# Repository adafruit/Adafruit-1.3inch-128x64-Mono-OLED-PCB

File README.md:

# PCB for the Adafruit 128x64 I2C/SPI 1.3" OLED breakout board

<a href="http://www.adafruit.com/products/938"><br/>
<a href="http://www.adafruit.com/products/938"><br/>
  Click here to purchase one from the Adafruit shop</a>

__Format is EagleCAD schematic and board layout__

These displays are small, only about 1.3" diagonal, but very readable due to the high contrast of an OLED display. This display is made of 128x64 individual white OLED pixels, each one is turned on or off by the controller chip. Because the display makes its own light, no backlight is required. This reduces the power required to run the OLED and is why the display has such high contrast; we really like this miniature display for its crispness!

The driver chip, SSD1306 can communicate in two ways: I2C or SPI. The OLED itself require a 3.3V power supply and 3.3V logic levels for communication, but we include a 3.3V regulator and all pins are fully level shifted so you can use with 5V devices!

We've updated the design to add auto-reset circuitry so that the reset pin is optional. The default interface is now I2C not SPI - since it speaks I2C you can easily connect it up with just two wires (plus power and ground!).  We've even included SparkFun qwiic compatible STEMMA QT connectors for the I2C bus so you don't even need to solder! 

The power requirements depend a little on how much of the display is lit but on average the display uses about 40mA from the 3.3V supply. Built into the OLED driver is a simple switch-cap charge pump that turns 3.3v-5v into a high voltage drive for the OLEDs.

[We have a detailed tutorial and example code in the form of an Arduino library](http://learn.adafruit.com/monochrome-oled-breakouts) for text and graphics. You'll need a microcontroller with more than 1K of RAM since the display must be buffered. The library can print text, bitmaps, pixels, rectangles, circles and lines. It uses 1K of RAM since it needs to buffer the entire display but its very fast! The code is simple to adapt to any other microcontroller.

## License
Adafruit invests time and resources providing this open source design,
please support Adafruit and open-source hardware by purchasing
products from Adafruit!

Designed by Adafruit Industries.
Creative Commons Attribution, Share-Alike license, check license.txt for more information
All text above must be included in any redistribution

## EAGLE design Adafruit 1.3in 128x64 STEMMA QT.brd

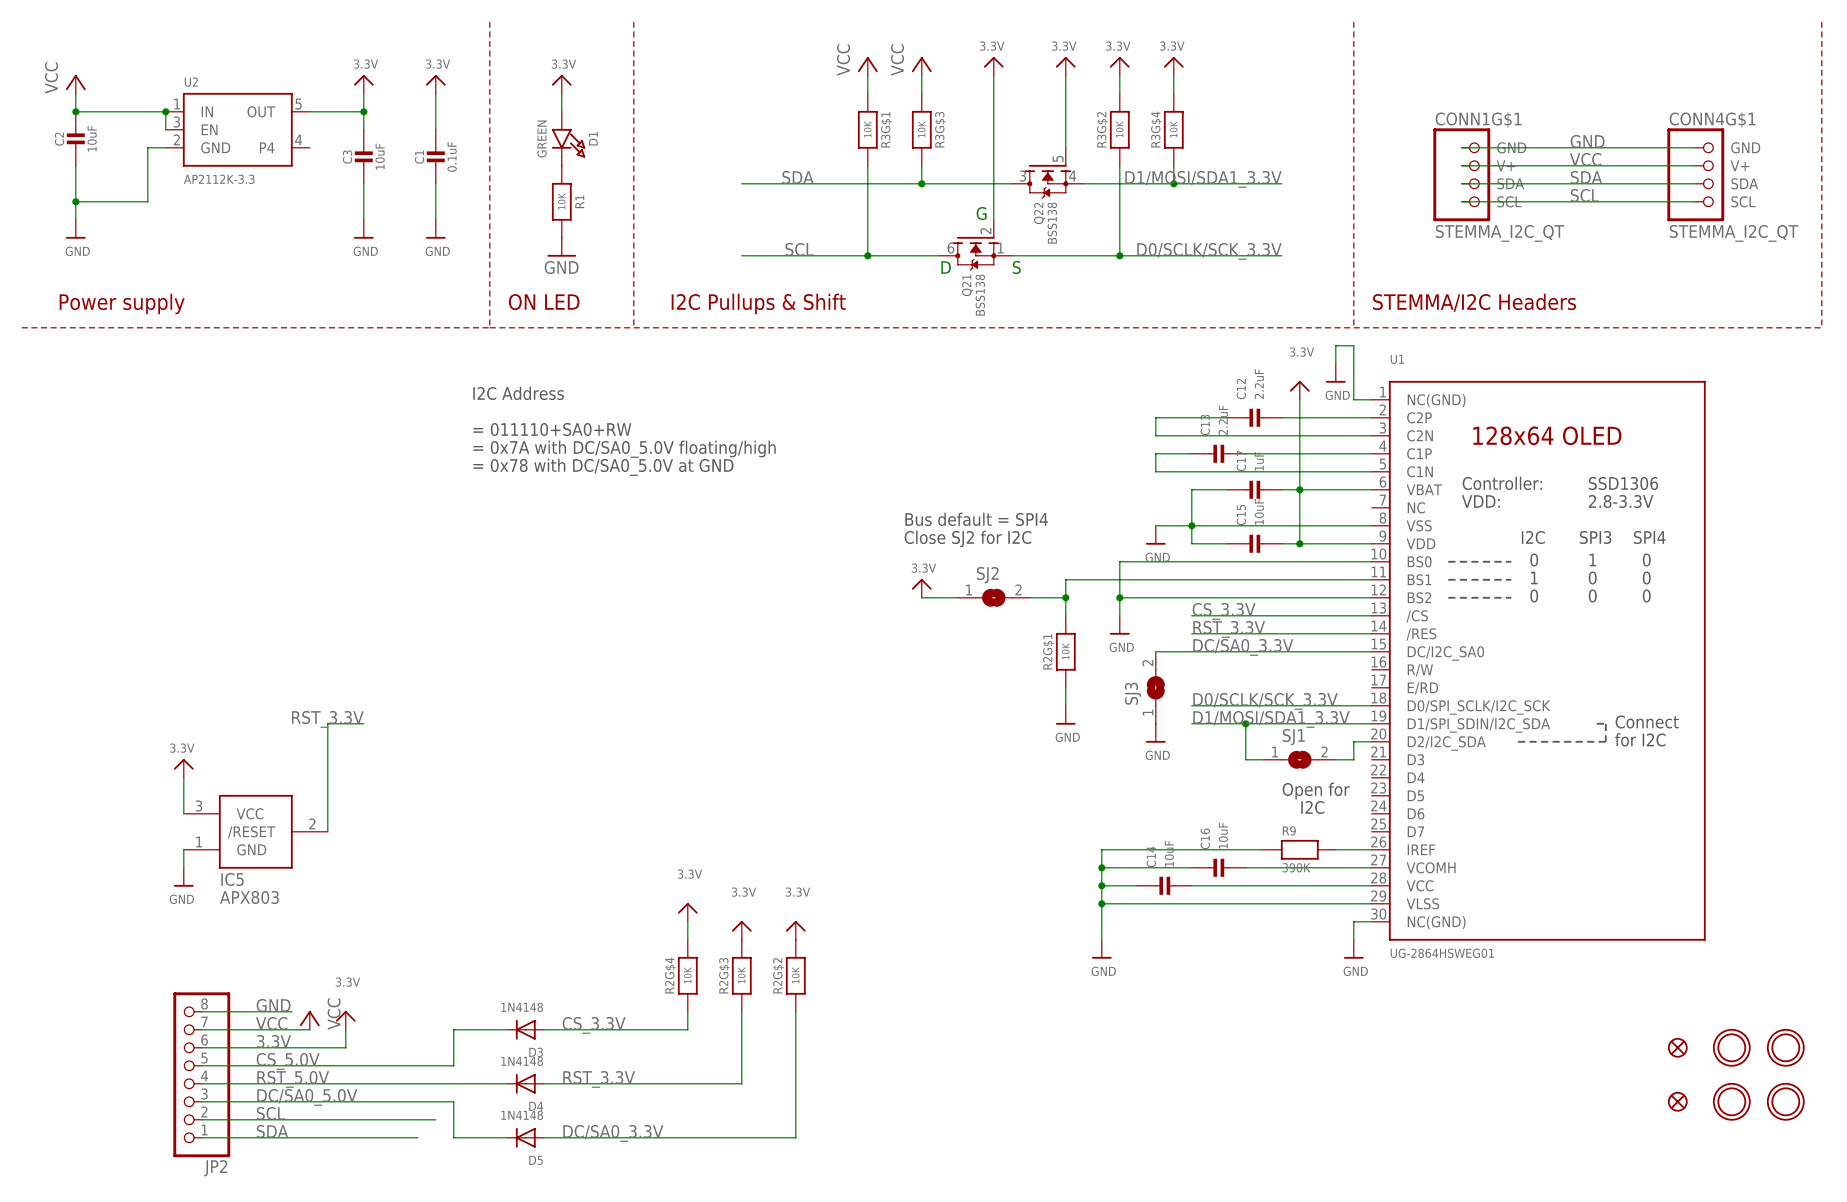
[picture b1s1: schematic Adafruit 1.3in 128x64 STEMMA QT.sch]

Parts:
C1: 0.1uF; 0603-NO
C2, C3, C14, C15, C16: 10uF; 0805-NO
C12, C13: 2.2uF; 0805-NO
C17: 1uF; 0603-NO
CONN1, CONN4: STEMMA_I2C_QT; JST_SH4
D1: GREEN; CHIPLED_0603_NOOUTLINE
D3, D4, D5: 1N4148; SOD-323
FID3, FID4: FIDUCIAL_1MM
IC5: APX803; SOT23
JP2: HEADER-1X870MIL; 1X08_ROUND_70
Q2: BSS138; SOT363
R1: 10K; 0603-NO
R2, R3: 10K; RESPACK_4X0603
R9: 390K; 0603-NO
SJ1, SJ2: SOLDERJUMPERCLOSED; SOLDERJUMPER_CLOSEDWIRE
SJ3: SOLDERJUMPER; SOLDERJUMPER_ARROW_NOPASTE
U1: UG-2864HSWEG01; UG-2864HSWEG01_1.3_WRAPAROUND
U2: AP2112K-3.3; SOT23-5
U$1, U$17, U$19, U$21: MOUNTINGHOLE2.5; MOUNTINGHOLE_2.5_PLATED

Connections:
3.3V: C1.1, C3.1, C15.2, C17.2, D1.A, IC5.3 (VCC), JP2.6, Q2.2 (G), Q2.5 (G), R2.5 (2), R2.6 (2), R2.7 (2), R3.2 (1), R3.4 (1), SJ2.1, U1.6 (VBAT), U1.9 (VDD), U2.5 (OUT)
CS_3.3V: D3.A, R2.4 (1), U1.13 (/CS)
CS_5.0V: D3.C, JP2.5
D0/SCLK/SCK_3.3V: Q2.1 (S), R3.7 (2), U1.18 (D0/SPI_SCLK/I2C_SCK)
D1/MOSI/SDA1_3.3V: Q2.4 (S), R3.5 (2), SJ1.1, U1.19 (D1/SPI_SDIN/I2C_SDA)
DC/SA0_3.3V: D5.A, R2.2 (1), SJ3.2, U1.15 (DC/I2C_SA0)
DC/SA0_5.0V: D5.C, JP2.3
GND: C1.2, C2.2, C3.2, C14.1, C15.1, C16.1, C17.1, CONN1.1 (GND), CONN4.1 (GND), IC5.1 (GND), JP2.8, R1.2, R2.1, R9.1, SJ3.1, U1.1 (NC(GND)), U1.8 (VSS), U1.10 (BS0), U1.12 (BS2), U1.29 (VLSS), U1.30 (NC(GND)), U2.2 (GND)
unnamed: D1.C, R1.1
unnamed: R2.8 (2), SJ2.2, U1.11 (BS1)
unnamed: R9.2, U1.26 (IREF)
unnamed: C12.2, U1.2 (C2P)
unnamed: C12.1, U1.3 (C2N)
unnamed: C13.2, U1.4 (C1P)
unnamed: C13.1, U1.5 (C1N)
unnamed: C14.2, U1.28 (VCC)
unnamed: C16.2, U1.27 (VCOMH)
unnamed: SJ1.2, U1.20 (D2/I2C_SDA)
RST_3.3V: D4.A, IC5.2 (/RESET), R2.3 (1), U1.14 (/RES)
RST_5.0V: D4.C, JP2.4
SCL: CONN1.4 (SCL), CONN4.4 (SCL), JP2.2, Q2.6 (D), R3.8 (2)
SDA: CONN1.3 (SDA), CONN4.3 (SDA), JP2.1, Q2.3 (D), R3.6 (2)
VCC: C2.1, CONN1.2 (V+), CONN4.2 (V+), JP2.7, R3.1, R3.3 (1), U2.1 (IN), U2.3 (EN)

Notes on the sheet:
I2C Pullups & Shift
STEMMA/I2C Headers
ON LED
Power supply
Bus default = SPI4
Close SJ2 for I2C
= 011110+SA0+RW
= 0x7A with DC/SA0_5.0V floating/high
= 0x78 with DC/SA0_5.0V at GND
I2C Address
Open for
I2C

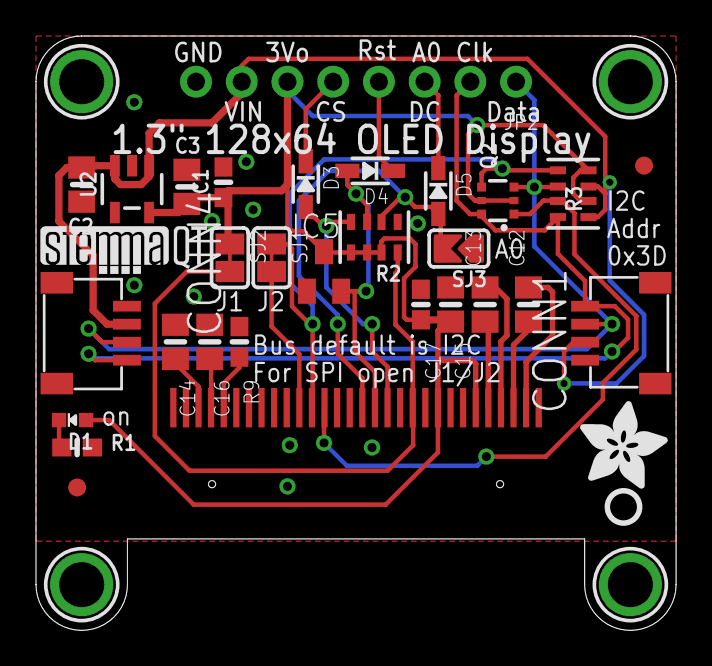
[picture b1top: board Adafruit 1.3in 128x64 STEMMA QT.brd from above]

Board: 2 copper layers, 35.6 x 33.0 mm, 36 parts (1 on the bottom side), 23 nets.

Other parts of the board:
U$8: ADAFRUIT_5MM
U$25: PCBFEAT-REV-040
U$31: STEMMAQT

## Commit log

2019-04-17 new readme + image
2020-10-19 Rename Adafruit_1.3_128x64_OLED.brd to Adafruit_1.3_128x64_OLED_Original.brd
2020-10-19 Rename Adafruit_1.3_128x64_OLED.sch to Adafruit_1.3_128x64_OLED_Original.sch
2020-10-19 Add STEMMA board files.
2020-10-19 Add asset
2020-10-19 Add STEMMA version.
2020-10-19 Rename Adafruit 1.3in 128x64 STEMMA QT.brd to Adafruit 1.3in 128x64 OLED STEMMA QT.brd
2020-10-19 Rename Adafruit 1.3in 128x64 STEMMA QT.sch to Adafruit 1.3in 128x64 OLED STEMMA QT.sch

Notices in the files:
parts and their libraries:
microbuilder: This work is placed in the public domain, and may be freely used for commercial and non-commercial work with the following conditions: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
